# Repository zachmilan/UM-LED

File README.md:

# UM-LED

UM-LED is a personal embedded systems project I am currently developing. The main idea is to build a cool remote control LED display (in the shape of the University of Michigan's "M") for my desk. This will be done by designing two PCB's - the remote and the display - and writing the firmware for each.

### Project Status 

March 9, 2026: The remote is complete and the firmware is in a consistent working state. Capacitive touch, BLE, haptics, motion detection, sleep timeout, charging and charging indicators, and low battery indicator all function as intended and have been integrated as a system. Changes to the remote's firmware will likely be made once the display is built and integrated, along with a few other polishing touches. Next step is the display PCB schematic. 

This is the first (and hopefully only) version of the remote PCB. Assembly was done using a stencil + hot-plate as well as hand soldering for necessary parts. Some rework and debugging was involved. 

Features, photos, and two short demo videos of the assembled remote exist below.

### Remote Features:
* **Capacitive Touch Pads:** Used for easy brightness control.
* **Accelerometer:** Automatically wakes the remote when picked up.
* **Haptic Motor:** Provides clear tactile feedback for user interactions.
* **USB-C Rechargeable:** Self explanatory, but easily charged with a USB-C cord and indicates charging status via lights.
* **Low Battery Indication:** Red light informs user when remote needs to be charged.
  
| Top View | Bottom View |
| :---: | :---: |
|  |  |
| *The top contains the hardware and UI* | *The underside contains the battery and haptic motor (hot-glued)* |

<div align="center">

**Capacitive Touch Demo**

https://github.com/user-attachments/assets/bd866a0d-1efd-45fc-9129-0372a43028ab

*Each touch triggers an LED flash and haptic feedback (turn volume UP to hear haptics firing).*

**Remote Sleep Demo**

https://github.com/user-attachments/assets/c11abb02-e6e1-4325-9b7a-56cc4e109a6d

*The remote wakes upon movement, and falls back asleep after 10 seconds of inactivity.*

</div>

---

### More details
I wrote a full, more formal design proposal when beginning this project — see [UM-LED Design Proposal (PDF)](https://github.com/zachmilan/UM-LED/blob/main/docs/UM-LED%20Design%20Proposal%20(No%20Timeline).pdf). The main idea is still intact, though it may not reflect the full design once done (for example, the accelerometer was an afterthought and hence not included in the proposal).

Or, if you just want to get an idea of the general system architecture, see below: 

| Remote Architecture | Display Architecture |
| :---: | :---: |
|  |  |
| *Signal flow for the remote, including the MCU, sensors, and haptic feedback.* | *System architecture for the LED display, including MCU, sensors, and power regulation.* |

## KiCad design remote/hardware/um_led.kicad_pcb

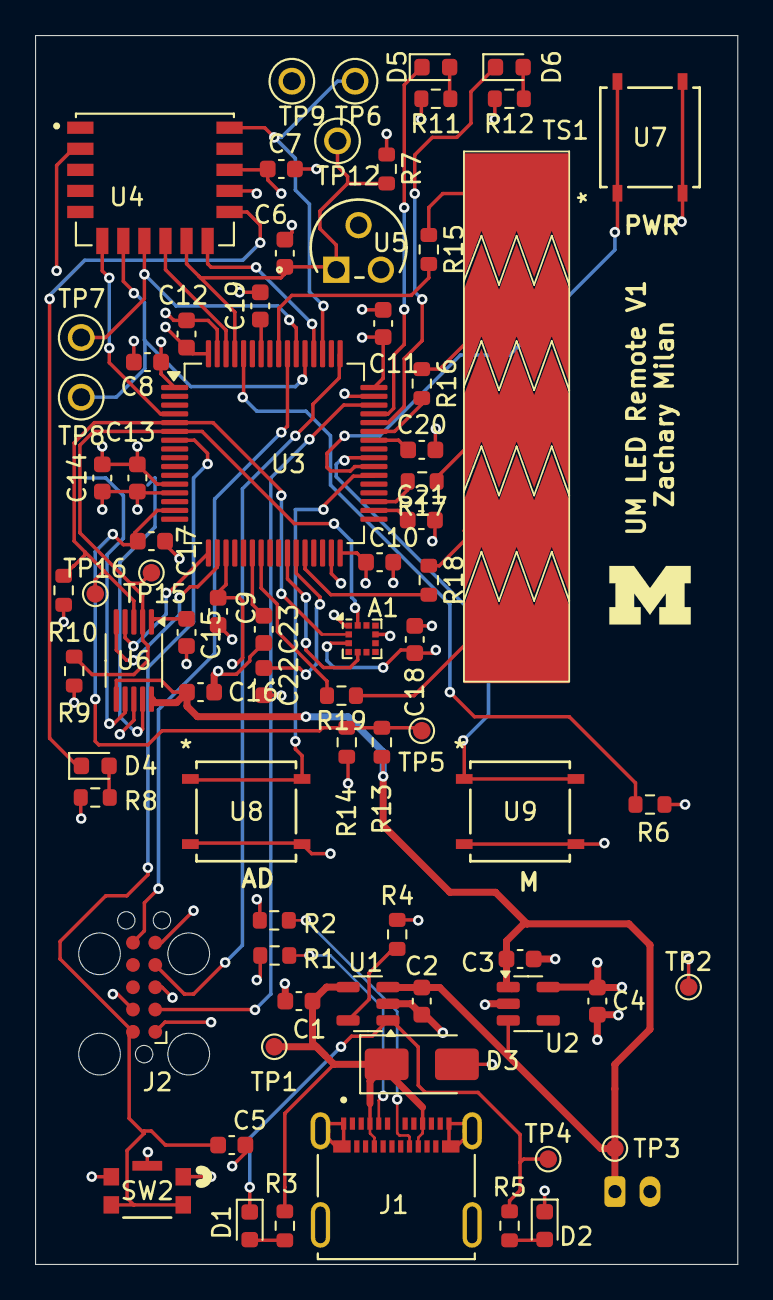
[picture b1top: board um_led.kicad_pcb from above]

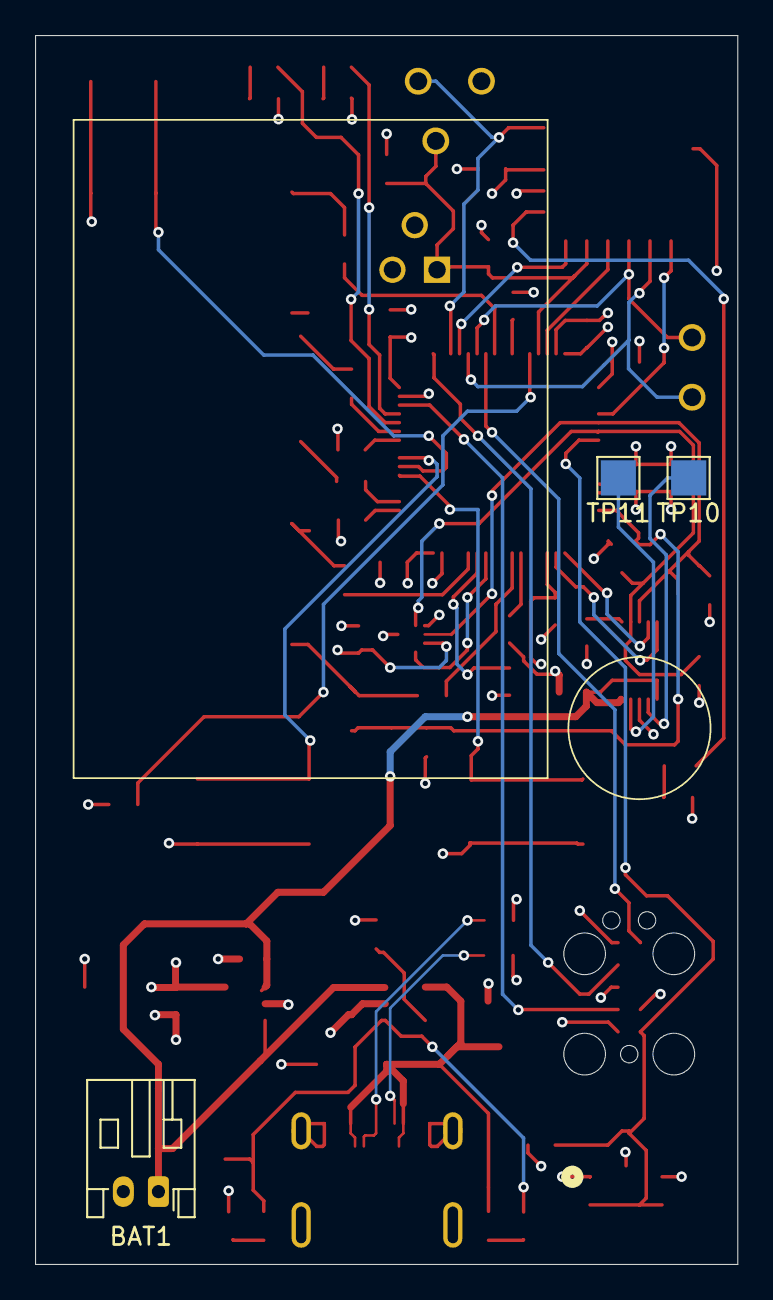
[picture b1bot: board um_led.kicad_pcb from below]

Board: 4 copper layers, 40.0 x 70.0 mm, 77 parts (3 on the bottom side), 55 nets.

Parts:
A1: MC3416; LGA-12_2x2mm_P0.5mm
BAT1: BATTERY; JST_PH_S2B-PH-K_1x02_P2.00mm_Horizontal
C1, C2, C12: 4.7uF; C_0603_1608Metric
C3, C4, C6, C14, C15, C16: 1uF; C_0603_1608Metric
C5, C18: 0.1uF; C_0603_1608Metric
C7: 10uF; C_0603_1608Metric
C8, C9, C10, C11, C17: 100nF; C_0603_1608Metric
C13: 10nF; C_0603_1608Metric
C19, C20, C21, C22, C23: 47nF; C_0603_1608Metric
D1: LED_OR; LED_0603_1608Metric
D2: LED_GR; LED_0603_1608Metric
D3: SMAJ5.0A; D_SMA
D4: LED_WHITE; LED_0603_1608Metric
D5: LED_RED; LED_0603_1608Metric
D6: LED_BLUE; LED_0603_1608Metric
J1: 10152803-00011LF; AMPHENOL_10152803-00011LF
J2: TC2050; Tag-Connect_TC2050-IDC-FP_2x05_P1.27mm_Vertical
R1, R2: 5.1K; R_0603_1608Metric
R3, R5: 820; R_0603_1608Metric
R4: 8.2K; R_0603_1608Metric
R6, R9, R10: 10K; R_0603_1608Metric
R7: 4.7K; R_0603_1608Metric
R8: 330; R_0603_1608Metric
R11: 560; R_0603_1608Metric
R12: 240; R_0603_1608Metric
R13: 270K; R_0603_1608Metric
R14: 1M; R_0603_1608Metric
R15, R16, R17, R18, R19: 1K; R_0603_1608Metric
SW2: KMR231GLFS; KMR2xxG_CNK
TP1: TEST_VBUS; TestPoint_Pad_D1.0mm
TP2: TEST_3V3; TestPoint_Pad_D1.0mm
TP3: TEST_BATT; TestPoint_Pad_D1.0mm
TP4: TEST_STAT; TestPoint_Pad_D1.0mm
TP5: TEST_ADC; TestPoint_Pad_D1.0mm
TP6, TP7, TP8, TP9, TP12: 5001; KEYSTONE_5001
TP10: LRA+; TestPoint_Pad_2.0x2.0mm
TP11: LRA-; TestPoint_Pad_2.0x2.0mm
TP15: TEST_SCL; TestPoint_Pad_D1.0mm
TP16: TEST_SDA; TestPoint_Pad_D1.0mm
TS1: 5S; TouchSlider-5_30x6mm
U1: MCP73831-2-OT; SOT-23-5
U2: TLV75533PDBV; SOT-23-5
U3: STM32F303RCTx; LQFP-64_10x10mm_P0.5mm
U4: BM71BLES1FC2-0B04AA; XCVR_BM71BLES1FC2-0B04AA
U5: MCP111-195I/TO; TO-92_MC_MCH
U6: DRV2605LDGS; VSSOP-10_3x3mm_P0.5mm
U7, U8, U9: PTS526 SK15 SMTR2 LFS; SMT_FS

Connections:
+3.3V: A1.3 (VDD), C4.1, C7.1, C8.2, C9.2, C10.2, C11.2, C12.2, C13.1, C14.1, C18.1, J2.1, R7.1, R8.2, R9.1, R10.1, R11.2, R12.2, TP2.1, U2.5 (OUT), U3.1 (VBAT), U3.13 (VDDA), U3.19 (VDD), U3.32 (VDD), U3.48 (VDD), U3.64 (VDD), U4.14 (VBAT), U5.2 (VDD)
+5V: C1.2, D3.1 (A1), J1.A4 (VBUS_A), J1.A9 (VBUS_A__1), J1.B4 (VBUS_B), J1.B9 (VBUS_B__1), R3.1, TP1.1, U1.4 (V_{DD})
+BATT: BAT1.1, C2.2, C3.1, C16.2, R13.1, TP3.1, U1.3 (V_{BAT}), U2.1 (IN), U2.3 (EN), U6.6 (VDD/NC), U6.10 (VDD)
/MCU/ACC_INT: A1.5 (INTN), U3.26 (PB0)
/MCU/BLE_MODE: TP6.TP, U3.51 (PC10), U4.16 (P2_0)
/MCU/BLE_RST: C6.1, R7.2, TP12.TP, U3.61 (PB8), U4.10 (RST_N), U5.1 (VOUT)
/MCU/BLE_RX: TP8.TP, U3.53 (PC12), U4.7 (HCI_RXD)
/MCU/BLE_STATUS1: U3.52 (PC11), U4.11 (P0_0)
/MCU/BLE_STATUS2: U3.62 (PB9), U4.9 (P3_6)
/MCU/BLE_TX: TP7.TP, U3.54 (PD2), U4.8 (HCI_TXD)
/MCU/BLE_UART_RX_IND: U3.4 (PC15), U4.6 (P1_6)
/MCU/NRST: C5.2, J2.10, SW2.2, SW2.3, U3.7 (NRST)
/MCU/SWCLK: J2.4, U3.49 (PA14)
/MCU/SWDIO: J2.2, U3.46 (PA13)
/MCU/SWO: J2.6, U3.55 (PB3)
ADC1_IN2: C17.1, R13.2, R14.1, TP5.1, U3.15 (PA1)
AUTO_DIM: U3.38 (PC7), U8.1, U8.2
BATT_LOW: D5.1 (K), U3.45 (PA12)
BUT_PRESS: D6.1 (K), U3.44 (PA11)
GND: A1.1 (VPP), A1.9 (GND), BAT1.2, C1.1, C2.1, C3.2, C4.2, C5.1, C6.2, C7.2, C8.1, C9.1, C10.1, C11.1, C12.1, C13.2, C14.2, C15.1, C16.1, C17.2, C18.2, C19.2, C20.2, C21.2, C22.2, C23.2, D2.1 (K), D3.2 (A2), J1.A1 (GND_A), J1.A12 (GND_A__1), J1.B1 (GND_B), J1.B12 (GND_B__1), J1.S1 (SHIELD), J1.S2 (SHIELD__1), J1.S3 (SHIELD__2), J1.S4 (SHIELD__3), J2.3, J2.5, J2.9, R1.2, R2.1, R4.2, R6.1, R14.2, SW2.1, SW2.4, SW2.5, TP9.TP, U1.2 (V_{SS}), U2.2 (GND), U3.12 (VSSA), U3.31 (VSS), U3.47 (VSS), U3.63 (VSS), U4.2 (GND), U4.13 (GND), U5.3 (VSS), U6.8 (GND), U7.3, U7.4, U8.3, U8.4, U9.3, U9.4
I2C2_SCL: A1.12 (SCL), R9.2, TP15.1, U3.6 (PF1), U6.2 (SCL)
I2C2_SDA: A1.2 (SDA), R10.2, TP16.1, U3.5 (PF0), U6.3 (SDA)
LRA_EN: U3.18 (PF4), U6.5 (EN)
LRA_TRIG: U3.17 (PA3), U6.4 (IN/TRIG)
MODE: U3.40 (PC9), U9.1, U9.2
unnamed: D1.2 (A), R3.2
unnamed: D1.1 (K), R5.1, TP4.1, U1.1 (STAT)
unnamed: D2.2 (A), R5.2
unnamed: D4.2 (A), R8.1
unnamed: D4.1 (K), U4.12 (P0_2/LED)
unnamed: D5.2 (A), R11.1
unnamed: D6.2 (A), R12.1
unnamed: J1.A5 (CC1), R1.1
unnamed: J1.B5 (CC2), R2.2
unnamed: R15.1, TS1.1 (TSC1)
unnamed: R16.1, TS1.2 (TSC2)
unnamed: R17.1, TS1.3 (TSC3)
unnamed: R18.1, TS1.4 (TSC4)
unnamed: R19.1, TS1.5 (TSC5)
unnamed: R4.1, U1.5 (PROG)
unnamed: R6.2, U3.60 (BOOT0)
unnamed: C23.1, U3.22 (PA6)
unnamed: C20.1, U3.42 (PA9)
unnamed: C22.1, U3.27 (PB1)
unnamed: C19.1, U3.58 (PB6)
unnamed: C21.1, U3.34 (PB13)
unnamed: TP10.1, U6.7 (OUT+)
unnamed: TP11.1, U6.9 (OUT-)
unnamed: C15.2, U6.1 (REG)
POWER: U3.39 (PC8), U7.1, U7.2
TSC_1: R15.2, U3.56 (PB4)
TSC_2: R16.2, U3.43 (PA10)
TSC_3: R17.2, U3.35 (PB14)
TSC_4: R18.2, U3.28 (PB2)
TSC_5: R19.2, U3.23 (PA7)

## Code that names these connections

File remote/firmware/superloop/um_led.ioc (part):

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Mcu.Name=STM32F303R(B-C)Tx
Mcu.Package=LQFP64
Mcu.UserName=STM32F303RCTx
PA1.GPIOParameters=GPIO_PuPd,GPIO_Label,GPIO_Mode
PA1.GPIO_Label=BATT_ADC
PA1.GPIO_Mode=GPIO_MODE_ANALOG
PA1.GPIO_PuPd=GPIO_NOPULL
PA1.Mode=IN2-Single-Ended
PA1.Signal=ADC1_IN2
PA10.Mode=G4_IO2-Channel
PA10.Signal=TSC_G4_IO2
PA11.GPIOParameters=PinState,GPIO_Label
PA11.GPIO_Label=BUTTN_PRESS_LED
PA11.PinState=GPIO_PIN_SET
PA11.Signal=GPIO_Output
PA12.GPIOParameters=PinState,GPIO_Label
PA12.GPIO_Label=LOW_BATT_LED
PA12.PinState=GPIO_PIN_SET
PA12.Signal=GPIO_Output
PA13.Mode=Trace_Asynchronous_SW
PA13.Signal=SYS_JTMS-SWDIO
PA14.Mode=Trace_Asynchronous_SW
PA14.Signal=SYS_JTCK-SWCLK
PA3.GPIOParameters=GPIO_Label
PA3.GPIO_Label=LRA_TRIG
PA3.Signal=GPIO_Output
PA6.Mode=G2_IO3-Sampling
PA6.Signal=TSC_G2_IO3
PA7.Mode=G2_IO4-Channel
PA7.Signal=TSC_G2_IO4
PA9.Mode=G4_IO1-Sampling
PA9.Signal=TSC_G4_IO1
PB0.GPIOParameters=GPIO_Label,GPIO_ModeDefaultEXTI
PB0.GPIO_Label=ACC_INT
PB0.GPIO_ModeDefaultEXTI=GPIO_MODE_IT_RISING
PB0.Signal=GPXTI0
PB1.Mode=G3_IO3-Sampling
PB1.Signal=TSC_G3_IO3
PB13.Mode=G6_IO3-Sampling
PB13.Signal=TSC_G6_IO3
PB14.Mode=G6_IO4-Channel
PB14.Signal=TSC_G6_IO4
PB2.Mode=G3_IO4-Channel
PB2.Signal=TSC_G3_IO4
PB3.Mode=Trace_Asynchronous_SW
PB3.Signal=SYS_JTDO-TRACESWO
PB4.Mode=G5_IO2-Channel
PB4.Signal=TSC_G5_IO2
PB6.Mode=G5_IO3-Sampling
PB6.Signal=TSC_G5_IO3
PB8.GPIOParameters=PinState,GPIO_PuPd,GPIO_Label,GPIO_ModeDefaultOutputPP
PB8.GPIO_Label=BLE_RST_N
PB8.GPIO_ModeDefaultOutputPP=GPIO_MODE_OUTPUT_OD
PB8.GPIO_PuPd=GPIO_NOPULL
PB8.PinState=GPIO_PIN_SET
PB8.Signal=GPIO_Output
PB9.GPIOParameters=GPIO_Label
PB9.GPIO_Label=BLE_STATUS2_IND
PB9.Signal=GPIO_Input
PC10.GPIOParameters=PinState,GPIO_PuPd,GPIO_Label,GPIO_ModeDefaultOutputPP
PC10.GPIO_Label=BLE_MODE
PC10.GPIO_ModeDefaultOutputPP=GPIO_MODE_OUTPUT_OD
PC10.GPIO_PuPd=GPIO_NOPULL
PC10.PinState=GPIO_PIN_SET
PC10.Signal=GPIO_Output
PC11.GPIOParameters=GPIO_Label
PC11.GPIO_Label=BLE_STATUS1_IND 
PC11.Signal=GPIO_Input
PC12.Mode=Asynchronous
PC12.Signal=UART5_TX
PC15-OSC32_OUT.GPIOParameters=GPIO_Label
PC15-OSC32_OUT.GPIO_Label=UART_RX_IND
PC15-OSC32_OUT.Signal=GPIO_Output
PC7.GPIOParameters=GPIO_PuPd,GPIO_Label,GPIO_ModeDefaultEXTI
PC7.GPIO_Label=AUTO_DIM
PC7.GPIO_ModeDefaultEXTI=GPIO_MODE_IT_FALLING
PC7.GPIO_PuPd=GPIO_PULLUP
PC7.Signal=GPXTI7
PC8.GPIOParameters=GPIO_PuPd,GPIO_Label,GPIO_ModeDefaultEXTI
PC8.GPIO_Label=PWR_BUTTON
PC8.GPIO_ModeDefaultEXTI=GPIO_MODE_IT_FALLING
PC8.GPIO_PuPd=GPIO_PULLUP
PC8.Signal=GPXTI8
PC9.GPIOParameters=GPIO_PuPd,GPIO_Label,GPIO_ModeDefaultEXTI
PC9.GPIO_Label=MODE_BUTTON
PC9.GPIO_ModeDefaultEXTI=GPIO_MODE_IT_FALLING
PC9.GPIO_PuPd=GPIO_PULLUP
PC9.Signal=GPXTI9
PD2.Mode=Asynchronous
PD2.Signal=UART5_RX
PF0-OSC_IN.GPIOParameters=GPIO_Pu,GPIO_Mode
PF0-OSC_IN.GPIO_Mode=GPIO_MODE_AF_OD
PF0-OSC_IN.GPIO_Pu=GPIO_NOPULL
PF0-OSC_IN.Mode=I2C
PF0-OSC_IN.Signal=I2C2_SDA
PF1-OSC_OUT.Mode=I2C
PF1-OSC_OUT.Signal=I2C2_SCL
PF4.GPIOParameters=PinState,GPIO_Label
PF4.GPIO_Label=LRA_EN
PF4.PinState=GPIO_PIN_SET
PF4.Signal=GPIO_Output
RCC.HSEPLLFreq_Value=8000000
RCC.HSE_VALUE=8000000
RCC.SYSCLKFreq_VALUE=8000000
board=custom

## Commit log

2025-11-26 Rename UM-LED Design Proposal.pdf to UM-LED Initial Design Proposal.pdf
2026-03-09 add video showcasing remote touch feature
    turn volume up to hear haptics firing
2026-03-09 test video in readme
2026-03-09 Add KiCad hardware files for remote (done) and display (beginning)
2026-03-09 Add display gitignore and remove auto-generated files
2026-03-09 add firmware files for remote superloop and rtos. changed top levels to remote and display
2026-03-09 create display firmware directory
